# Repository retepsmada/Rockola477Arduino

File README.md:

# Rockola477Arduino
The software for a custom arduino controller for the Rockola 477

Based on the information from Jim Hawkridge at https://jim.hawkridges.co.uk/projects/juke/ and https://github.com/jimhawkridge/rockola477/tree/master

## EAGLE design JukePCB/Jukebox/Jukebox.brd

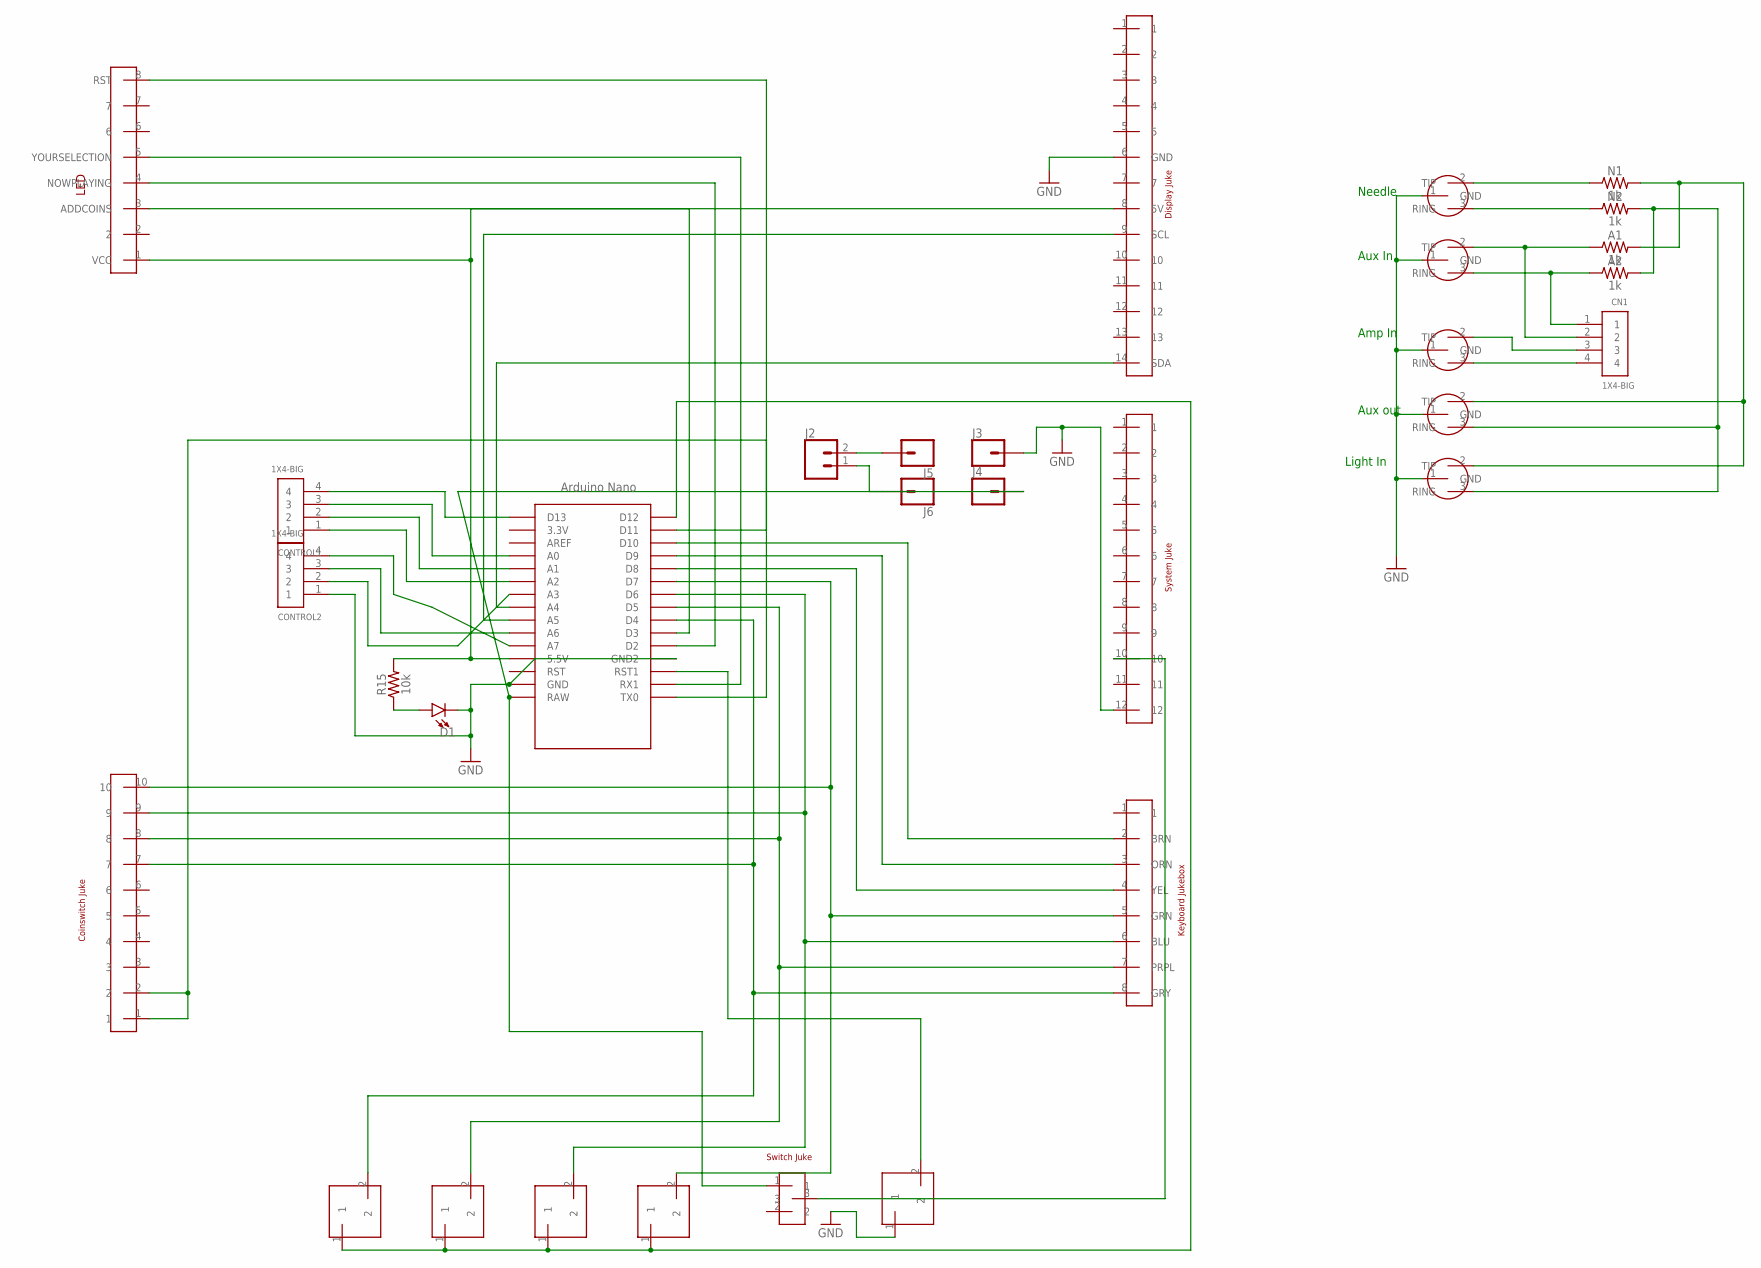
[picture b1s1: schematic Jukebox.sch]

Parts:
A1, A2: 1k; AXIAL-0.3
AUXIN: JUKEHEADPHONE
AUXOUT: JUKEHEADPHONE
CN1: 1X4-BIG; 1X04-BIG
CONTROL1, CONTROL2: 1X4-BIG; 1X04-BIG
D1: LED5MM; LED_5MM
FROMNEEDLE: JUKEHEADPHONE
J2: CONN_02; 1X02
J3, J4, J5, J6: CONN_01; 1X01
N1, N2: 1k; AXIAL-0.3
R15: 10k; AXIAL-0.3
TOAMP: JUKEHEADPHONE
TOLIGHT: JUKEHEADPHONE
U$1: NANO
U$5: 10PINJUKE
U$6: 8PINJUKE
U$7: 14PINJUKE
U$8: 12PINJUKE
U$9, U$10, U$11, U$12, U$13: JUKEBUTTON
U$14: JUKESWITCH
U$17: 8PINJUKE2; 8PINJUKE

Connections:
GND: AUXIN.1 (GND), AUXOUT.1 (GND), CONTROL2.1, D1.K (C), FROMNEEDLE.1 (GND), J3.1, TOAMP.1 (GND), TOLIGHT.1 (GND), U$1.GND, U$1.GND1 (GND2), U$7.6 (GND), U$8.12, U$13.1
unnamed: U$1.D4, U$5.7, U$6.8 (GRY), U$9.2
unnamed: U$1.D5, U$5.8, U$6.7 (PRPL), U$10.2
unnamed: U$1.D6, U$5.9, U$6.6 (BLU), U$11.2
unnamed: U$1.D7, U$5.10, U$6.5 (GRN), U$12.2
unnamed: U$1.D8, U$6.4 (YEL)
unnamed: U$1.D9, U$6.3 (ORN)
unnamed: U$1.D10, U$6.2 (BRN)
unnamed: U$8.10, U$14.3
unnamed: U$1.RST1, U$13.2
unnamed: U$1.D12, U$9.1, U$10.1, U$11.1, U$12.1
unnamed: U$1.D11, U$5.1, U$5.2
unnamed: U$1.A4, U$7.14 (SDA)
unnamed: CN1.3, TOAMP.2 (TIP)
unnamed: CN1.4, TOAMP.3 (RING)
unnamed: J2.2, J5.1
unnamed: FROMNEEDLE.3 (RING), N2.P$1 (1)
unnamed: FROMNEEDLE.2 (TIP), N1.P$1 (1)
unnamed: A1.P$1 (1), AUXIN.2 (TIP), CN1.2
unnamed: A2.P$1 (1), AUXIN.3 (RING), CN1.1
unnamed: J2.1, J6.1
unnamed: U$1.A5, U$7.9 (SCL)
unnamed: U$1.D3, U$17.3 (ADDCOINS)
unnamed: A2.P$2 (2), AUXOUT.3 (RING), N2.P$2 (2), TOLIGHT.3 (RING)
unnamed: A1.P$2 (2), AUXOUT.2 (TIP), N1.P$2 (2), TOLIGHT.2 (TIP)
unnamed: U$1.D2, U$17.4 (NOWPLAYING)
unnamed: CONTROL1.4, U$1.D13
unnamed: R15.P$2 (2), U$1.5V (5.5V), U$7.8 (5V), U$17.1 (VCC)
unnamed: CONTROL1.3, U$1.A0
unnamed: CONTROL1.2, U$1.A1
unnamed: CONTROL1.1, U$1.A2
unnamed: CONTROL2.4, U$1.A7
unnamed: J4.1, U$1.RAW, U$14.1
unnamed: D1.A, R15.P$1 (1)
unnamed: U$1.RX1, U$17.5 (YOURSELECTION)
unnamed: CONTROL2.3, U$1.A6
unnamed: CONTROL2.2, U$1.A3
unnamed: U$1.TX0, U$17.8 (RST)

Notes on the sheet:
Aux In
Needle
Amp In
Light In
Aux out

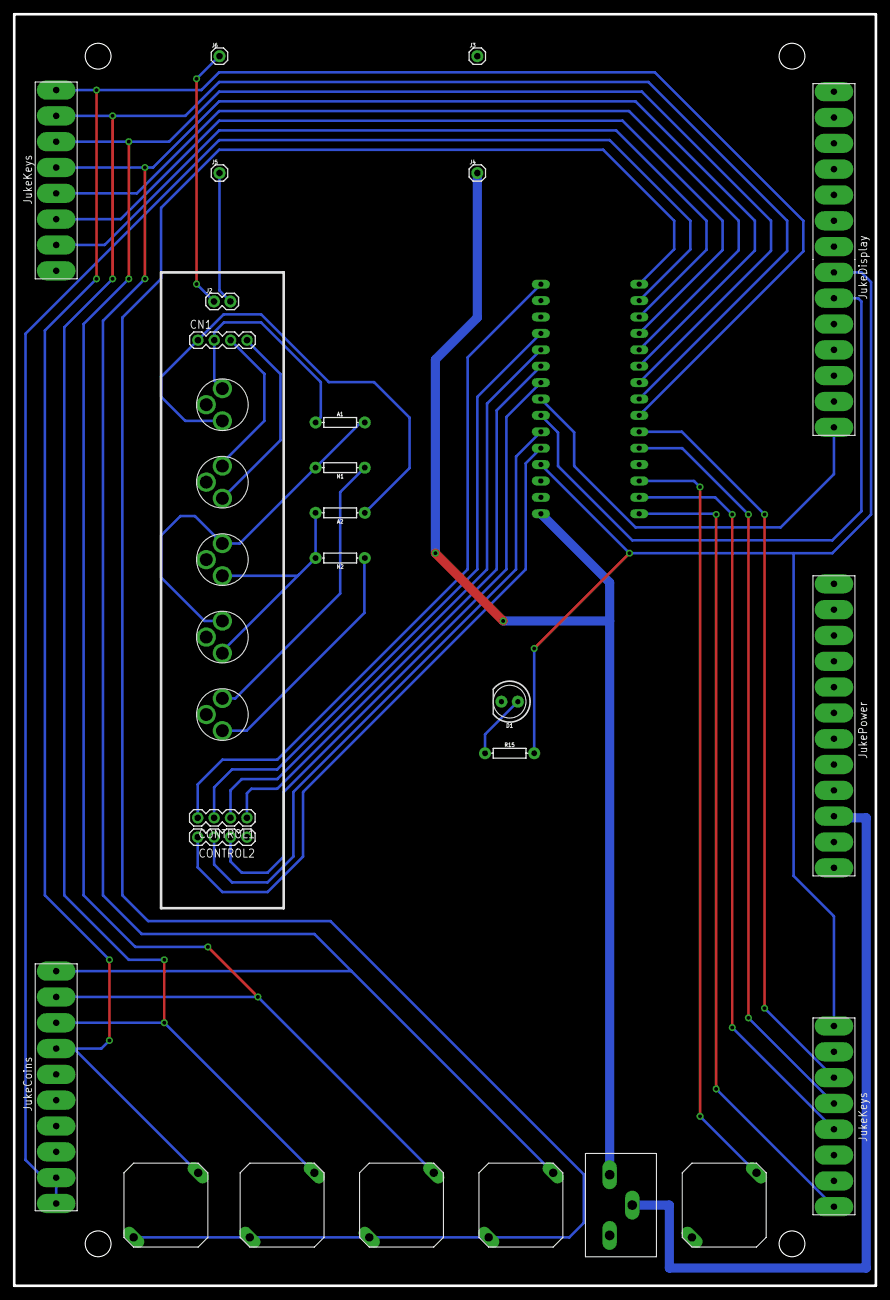
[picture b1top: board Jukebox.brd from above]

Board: 2 copper layers, 133.5 x 197.0 mm, 31 parts (0 on the bottom side), 38 nets.

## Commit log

2016-09-18 First Draft of Code - Only Some Variables
2016-09-18 First Draft of Code Update
2016-09-18 Changed int to define
2016-09-18 Actually used define correctly lol
2016-09-18 reset
2016-09-18 Update 9/18/16 2:03 PM
2016-09-18 Test to see if we can select a record
2016-09-19 removed =
2016-09-24 added semicolons
2016-09-24 Fixed comments and syntax error
2016-11-16 Added Pseudocode for Jukebox.ino
2016-11-24 Added code to interface with displays and keyboard
2016-11-24 Added printing the keyboard to credit display and clear display function
2016-11-24 Updated so that it works
2016-11-24 Revert "Updated so that it works"
    This reverts commit 182a2cdb171b9b936323514f542293d68d889d12.
2016-11-24 Revert "Revert "Updated so that it works""
    This reverts commit 38003abbb1d2ccf2c8adc12ebc05fc687149e05d.
2016-11-25 Now Saves record number current as variable and added Noble's convert function
2016-11-25 work on recordSelect function-needs checking
2016-11-26 Fixed recordSelect
2016-11-26 Added Money Function With nothing in it
2016-11-26 Update - fixes
2016-11-27 first Reset reselect implementation needs to be improved
2016-11-27 Test Program selects record 267
2016-11-27 Fixed Side selection and pulse number(maybe)
2016-11-28 Update Side and Pulse
2016-11-28 IT WORKS NOW YAY!
2016-11-29 Got rid of repeating code
2016-11-29 Revert "Got rid of repeating code"
    This reverts commit 83f149e090a615c922a8a5b4dde9f5f9a5d48677.
2016-11-29 Update Interrupt
2016-11-29 Temp integrated input into recordselect
2016-11-29 Fixed record select again.
2016-11-29 REVERT TO OLDER EVERYTHING IS BROKEN
2016-12-15 Fixed spacing in Jukebox Main Preliminary
2016-12-19 Shortened and commented Main ino
2017-01-01 attempt 1
2017-01-01 tast
2017-01-01 combined sketch nov and main
2017-01-01 WOOHOO CREDITS AND SHIT
2017-01-03 Moved some code around and figured out how to fix keypad
2017-01-04 Added queue and fixed releaseCount
2017-01-04 Fixed small bug,
    there is a glitch where after the first selection has been accepted, if
    you don’t hit the reset button, the selection only accepts 2 digits,
    with the second appearing in the middle of the display and only writing
    2 to the variable
2017-01-04 it onyl prints 2 and fixed that issure form before
2017-01-26 Added releaseCount back, need to test
2017-01-27 Update, blacklist
2017-01-27 Nathan sync
2017-02-06 Incomplete New Keypad, *DOESN'T WORK"
2017-02-07 Pin updates
2017-02-07 Need to use char for array
2017-02-07 Fixed Keyboard, but still needs work
2017-02-08 Pin update & release count update
2017-02-08 Pin updates and fixed some issues
2017-02-09 updat
2017-02-09 PUSH FUNCTION IS BROKEN RUN FOR THE HILLS
2017-02-09 Cleaned up code and possible fixed releaseCount
2017-02-09 Fixed typo in pop()
2017-02-09 Minor Updates/comments
2017-02-09 Added more debugging
2017-02-09 Possibly fixed issue
2017-02-09 Update, comments, fixed pulseCount, moved some code
2017-02-10 WHY GITHUB WHY
2017-02-10 Revert last commit
2017-02-10 Fixed recordSide and minor things
2017-02-11 Changes Pin ID's for board
2017-02-12 PCB update
2017-02-12 PCB UPDATE 2
2017-02-12 Added GND net
2017-02-12 Unlocked file
2017-02-13 smol update
2017-02-13 almost final schematic
2017-02-13 Huge board update
2017-02-13 board proto 1
2017-02-13 smol eagle
2017-02-14 almost final routes
2017-02-16 Anime.mp4
2017-02-17 sudo apt update
2017-02-20 Various desgin tweaks (see commit message)
    1.Re routed some traces to eliminate some jumpers.
    2. Ran ratsnest to fill in ground plane
    Note: I ran a DRC and it gave me a bunch of stop errors. This is becouse compontent silkscreens were confilcting with their pads. As we're not using a silk screen this should be fine
    Note: In the upper left hand side there's a jumper that looks like it goes no where. This is connedcting the ground plane of the audio jack to the rest of the board as it got enclosed.
2017-02-20 Update.exe
    I changed the ground trace so that the gound plane is intact and made
    the traces a little better
2017-02-20 Deleted Lock
2017-02-21 Board Update, Not Final
2017-02-21 Added not ground plane fixed some traces, need to fix audio bits
2017-02-22 Huge Sound Update, almost final
2017-02-22 Update, but recordplaying is very broken
2017-02-23 Fixed indentation and got rid of unnecessary braces
2017-02-23 removed my tests
2017-02-23 Added separate ino without while loops
2017-02-24 Moved No_While_loops to its own folder
2017-02-24 Probably final board
2017-02-28 gerber Files
2017-03-03 dxf yeah
2018-06-30 Started new board design
2018-06-30 Attempt to break up the project

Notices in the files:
parts and their libraries:
SparkFun-LED: Licensing: Creative Commons ShareAlike 4.0 International - https://creativecommons.org/licenses/by-sa/4.0
